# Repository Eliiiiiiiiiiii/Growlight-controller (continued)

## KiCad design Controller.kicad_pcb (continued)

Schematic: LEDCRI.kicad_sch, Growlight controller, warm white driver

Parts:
C501, C502, C504, C505, C506, C510, C518, C520, C521, C522: 10u; C 0805 (2012 Metric)
C503, C519: 22u; C_1206_3216Metric
C507: 47u; CP_Radial_D6.3mm_P2.50mm
C508: CFILT; C 0402 (1005 Metric); not fitted
C509: 2u2; C 0603 (1608 Metric)
C511, C512, C513, C515, C516, C517: TBD; C 0402 (1005 Metric); not fitted
C514: 1u; C 0402 (1005 Metric)
D501: SP1560L-A; TO-227B Dowo
JP501: Jumper_2_Small_Open; Jumper-NO 2P (1.9x1.4)
JP503: Jumper_2_Small_Open; PinHeader_1x02_P1.00mm_Vertical
L501: 22u; PDMTAT044125-220MWU
Q501, Q502: SI8487DB; WLCSP-4 (1.56x1.56) P0.8
Q503: BSC0805LS; DFN-8 (5x6) 1EP Infineon
R501: 20mΩ; R 1225 2w Kelvin
R502: 20k; R 0402 (1005 Metric)
R503: 10r; R 0603 (1608 Metric)
R504: 121k; R 0402 (1005 Metric)
R505: 40mΩ; R 1508 2w Kelvin
R506, R512: 10k; R 0402 (1005 Metric)
R507: 665k; R 0603 (1608 Metric)
R508: 57k6; R 0402 (1005 Metric)
R509, R510: 3k3; R 0402 (1005 Metric)
R511: 100k; R 0402 (1005 Metric)
R513: 34k8; R 0402 (1005 Metric)
R515: 5k76; R 0402 (1005 Metric)
R516: 3k92; R 0402 (1005 Metric)
R517, R518: 11k; R 0402 (1005 Metric)
R519: 52k3; R 0402 (1005 Metric)
R520: 6k; R 0402 (1005 Metric)
R521: 4k75; R 0402 (1005 Metric)
SW501: MINI 12C02; MINI MSK12CO2
U501: LP8866; QFN-32 (5x5) P0.5

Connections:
+3V3: C514.1, R509.1, R510.1, R511.1, R512.1, U501.22 (VDD); also elsewhere on the board
+HVLEDCRI: C504.1, C505.1, C506.1, C507.1, C520.1, C521.1, C522.1, D501.3 (K), R507.1; also elsewhere on the board
+PVDD: R501.4, R504.1; also elsewhere on the board
/LED CONNECTORS/-VLEDCRI.1: C513.1, U501.7 (OUT1); also elsewhere on the board
/LED CONNECTORS/-VLEDCRI.2: C517.1, U501.6 (OUT2); also elsewhere on the board
/LED CONNECTORS/-VLEDCRI.3: C512.1, U501.5 (OUT3); also elsewhere on the board
/LED CONNECTORS/-VLEDCRI.4: C516.1, U501.3 (OUT4); also elsewhere on the board
/LED CONNECTORS/-VLEDCRI.5: C511.1, U501.2 (OUT5); also elsewhere on the board
/LED CONNECTORS/-VLEDCRI.6: C515.1, U501.1 (OUT6); also elsewhere on the board
/LED DRIVERS/LED WW HIGH CRI/+VCPMP: C510.1, U501.26 (CPMP)
/LED DRIVERS/LED WW HIGH CRI/+VINSD: C501.1, C502.1, C503.1, C518.1, C519.1, L501.2, Q501.2 (D), Q501.3 (D), Q502.2 (D), Q502.3 (D)
/LED DRIVERS/LED WW HIGH CRI/+VINSNS: Q501.4 (S), Q502.4 (S), R501.1, R502.1
/LED DRIVERS/LED WW HIGH CRI/BFSET: R517.1, U501.16 (BFSET)
/LED DRIVERS/LED WW HIGH CRI/BSYNC: R512.2, U501.11 (BSYNC)
/LED DRIVERS/LED WW HIGH CRI/ISET: R513.2, R519.1, U501.31 (ISET)
/LED DRIVERS/LED WW HIGH CRI/LEDCRI.ANLG.CSN: R505.3, U501.30 (CSN)
/LED DRIVERS/LED WW HIGH CRI/LEDCRI.ANLG.CSP: R505.2, U501.29 (CSP)
/LED DRIVERS/LED WW HIGH CRI/LEDCRI.ANLG.FB: C508.1, R507.2, R508.1, U501.32 (FB)
/LED DRIVERS/LED WW HIGH CRI/LEDCRI.ANLG.UVLO: R504.2, R506.1, U501.18 (UVLO)
/LED DRIVERS/LED WW HIGH CRI/LEDCRI.ANLG.VSN: R501.2, U501.20 (VSN)
/LED DRIVERS/LED WW HIGH CRI/LEDCRI.ANLG.VSP: R501.3, U501.19 (VSP)
/LED DRIVERS/LED WW HIGH CRI/LEDCRI.SWN: D501.1 (A), D501.2 (A), L501.1, Q503.5 (D)
/LED DRIVERS/LED WW HIGH CRI/LSET: JP501.2 (B), R518.1, U501.14 (LSET)
/LED DRIVERS/LED WW HIGH CRI/MODE: R521.1, U501.17 (MODE)
/LED DRIVERS/LED WW HIGH CRI/PFSET: R515.1, R516.1, U501.15 (PFSET)
/LED DRIVERS/LED WW HIGH CRI/SD: Q501.1 (G), Q502.1 (G), R502.2, U501.21 (SD)
/LED DRIVERS/LEDCRI.EN: U501.23 (EN); also elsewhere on the board
/LED DRIVERS/LEDCRI.I2C0.SCL: R509.2, U501.10 (SCL); also elsewhere on the board
/LED DRIVERS/LEDCRI.I2C0.SDA: R510.2, U501.9 (SDA); also elsewhere on the board
/LED DRIVERS/LEDCRI.INT: R511.2, U501.8 (INT); also elsewhere on the board
/LED DRIVERS/LEDCRI.P.0: U501.12 (PWM); also elsewhere on the board
GND: C501.2, C502.2, C503.2, C504.2, C505.2, C506.2, C507.2, C508.2, C510.2, C511.2, C512.2, C513.2, C514.2, C515.2, C516.2, C517.2, C518.2, C519.2, C520.2, C521.2, C522.2, JP503.1 (A), R505.4, R506.2, R508.2, R517.2, R518.2, R519.2, R520.2, R521.2, SW501.2 (COM), U501.4 (LGND), U501.13 (SGND), U501.28 (PGND), U501.33 (EP); also elsewhere on the board
unnamed: JP501.1 (A), R520.1
unnamed: JP503.2 (B), R513.1
unnamed: Q503.4 (G), R503.2
unnamed: Q503.1 (S), Q503.2 (S), Q503.3 (S), R505.1
unnamed: R515.2, SW501.1 (C1)
unnamed: R516.2, SW501.3 (C2)
unnamed: C509.2, U501.24 (C1N)
unnamed: C509.1, U501.25 (C1P)
unnamed: R503.1, U501.27 (GD)

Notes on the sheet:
>1.25Ω
SPZ1HM470E08O00RA
RL3720WT-R040-FNH
For potential stability issues
Closed JP501 → 150mA Open JP501 → 60mA
Closed JP503 → 6CH Open JP501 → 2CH
PDMTAT044125-220MWU
Tie to GND if channel is unused
C3216X5R1V226MTJ00E
Hardware config
HoCS1225-3W-20mR-1%-TCR200
Can be fitted with ESD diodes

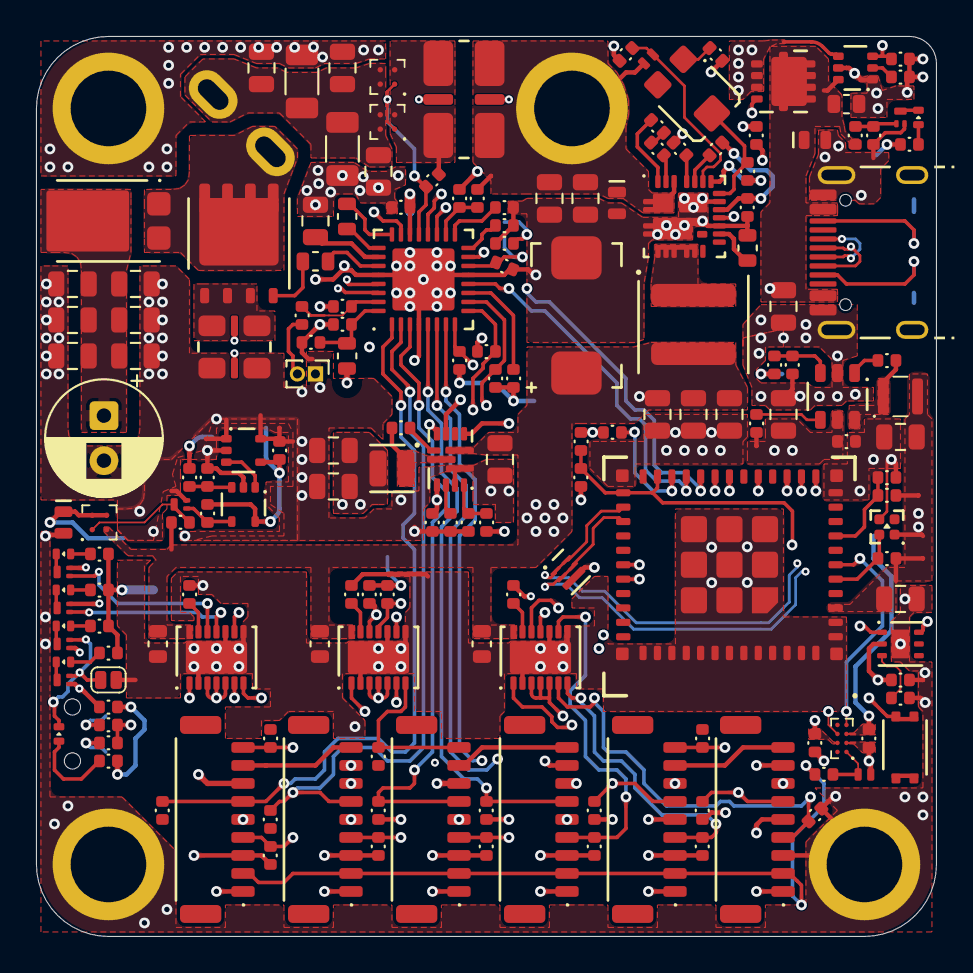
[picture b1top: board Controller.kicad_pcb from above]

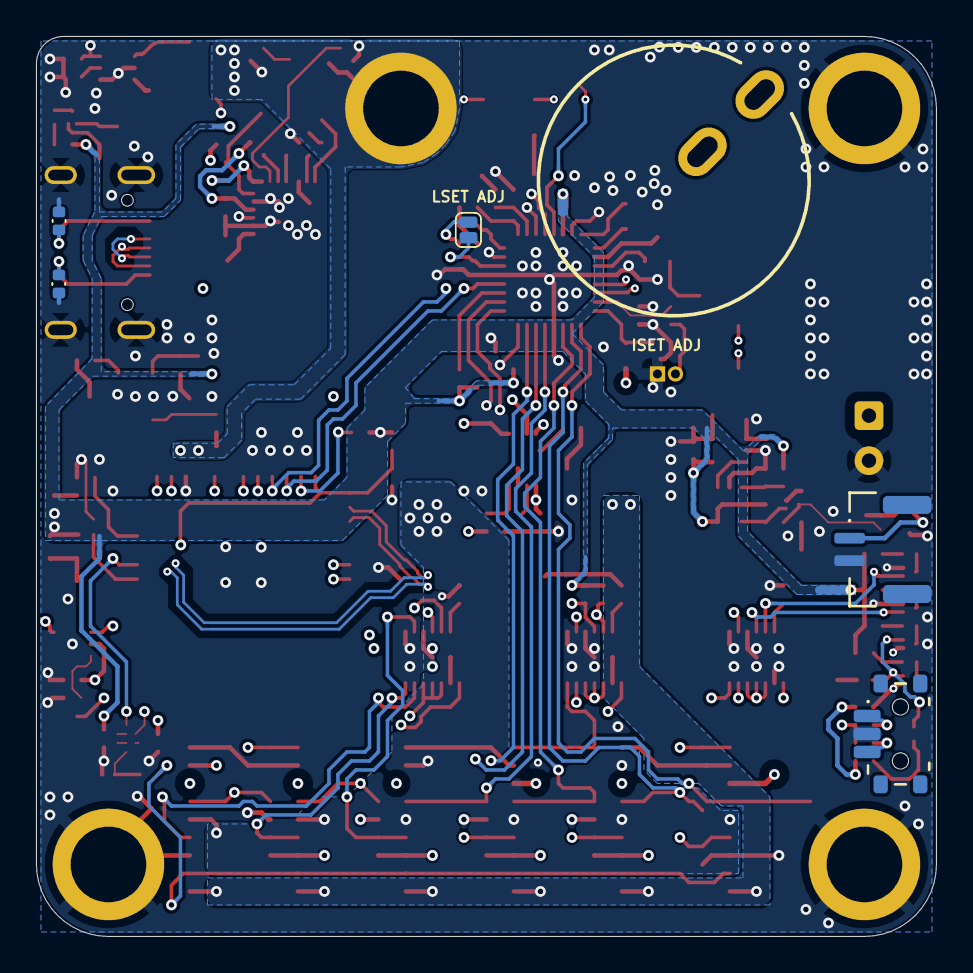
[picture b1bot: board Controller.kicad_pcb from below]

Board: 6 copper layers, 50.0 x 50.0 mm, 182 parts (6 on the bottom side), 119 nets.
